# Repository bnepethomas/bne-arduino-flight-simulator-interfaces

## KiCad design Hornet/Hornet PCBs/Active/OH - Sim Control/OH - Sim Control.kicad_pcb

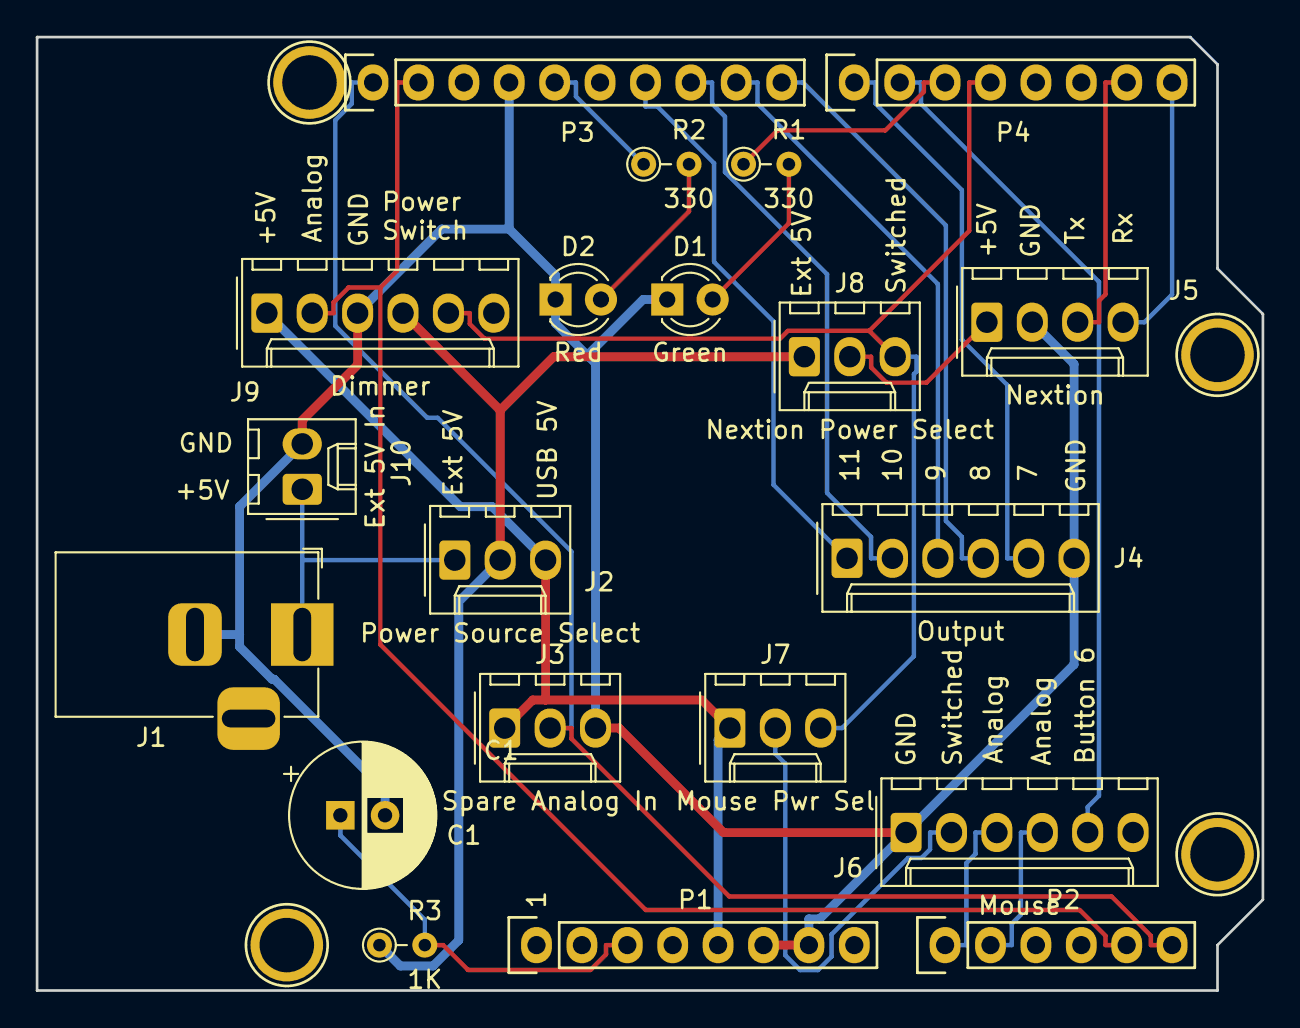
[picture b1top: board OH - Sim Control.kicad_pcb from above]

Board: 2 copper layers, 68.6 x 53.3 mm, 24 parts (0 on the bottom side), 24 nets.

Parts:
C1: CP; PT_CP_Radial_D8.0mm_P2.50mm
D1: Green; LED_D3.0mm
D2: Red; LED_D3.0mm
J1: Ext 5V In; BarrelJack_Horizontal
J2: Power Source Select; Molex_1x03_P2.54mm_Vertical
J3: Spare Analog In; Molex_1x03_P2.54mm_Vertical
J4: Output; Molex_1x06_P2.54mm_Vertical
J5: Nextion; Molex_1x04_P2.54mm_Vertical
J6: Mouse; Molex_1x06_P2.54mm_Vertical
J7: Mouse Pwr Sel; Molex_1x03_P2.54mm_Vertical
J8: Nextion Power Select; Molex_1x03_P2.54mm_Vertical
J9: Dimmer; Molex_1x06_P2.54mm_Vertical
J10: Ext 5V In; Molex_1x02_P2.54mm_Vertical
P1: Power; Socket_Strip_Arduino_1x08
P2: Analog; Socket_Strip_Arduino_1x06
P3: Digital; Socket_Strip_Arduino_1x10
P4: Digital; Socket_Strip_Arduino_1x08
P5, P6, P7, P8: CONN_01X01; Arduino_1pin
R1, R2: 330; PT_R_Axial_DIN0204_L3.6mm_D1.6mm_P2.54mm_Vertical
R3: 1K; PT_R_Axial_DIN0204_L3.6mm_D1.6mm_P2.54mm_Vertical

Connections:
+5V: J2.3, J3.1, J7.1, J9.1, P1.5
+5VD: J2.2, J8.1, J9.4, R3.1
/0(Rx): J5.4, P4.8
/1(Tx): J5.3, P4.7
/5(**): P4.3, R1.1
/6: J6.5, P4.2
/7: J4.5, P4.1
/8: J4.4, P3.10
/9: J4.3, P3.9
/10: J4.2, P3.8
/11: J4.1, P3.7
/13(SCK): P3.5, R2.1
/A0: J6.3, P2.1
/A1: J6.4, P2.2
/A4(SDA): J9.2, P2.5, P3.2
/A5(SCL): J3.2, P2.6, P3.1
/Reset: C1.1, P1.3, R3.2
/Swtiched_5VD: J7.3, J8.3, J9.5, P4.4
GND: C1.2, D1.1, D2.1, J1.2, J3.3, J4.6, J5.2, J6.1, J9.3, J10.2, P1.6, P1.7, P3.4
unnamed: D1.2, R1.2
unnamed: D2.2, R2.2
unnamed: J1.1, J2.1, J10.1
unnamed: J5.1, J8.2
unnamed: J6.2, J7.2

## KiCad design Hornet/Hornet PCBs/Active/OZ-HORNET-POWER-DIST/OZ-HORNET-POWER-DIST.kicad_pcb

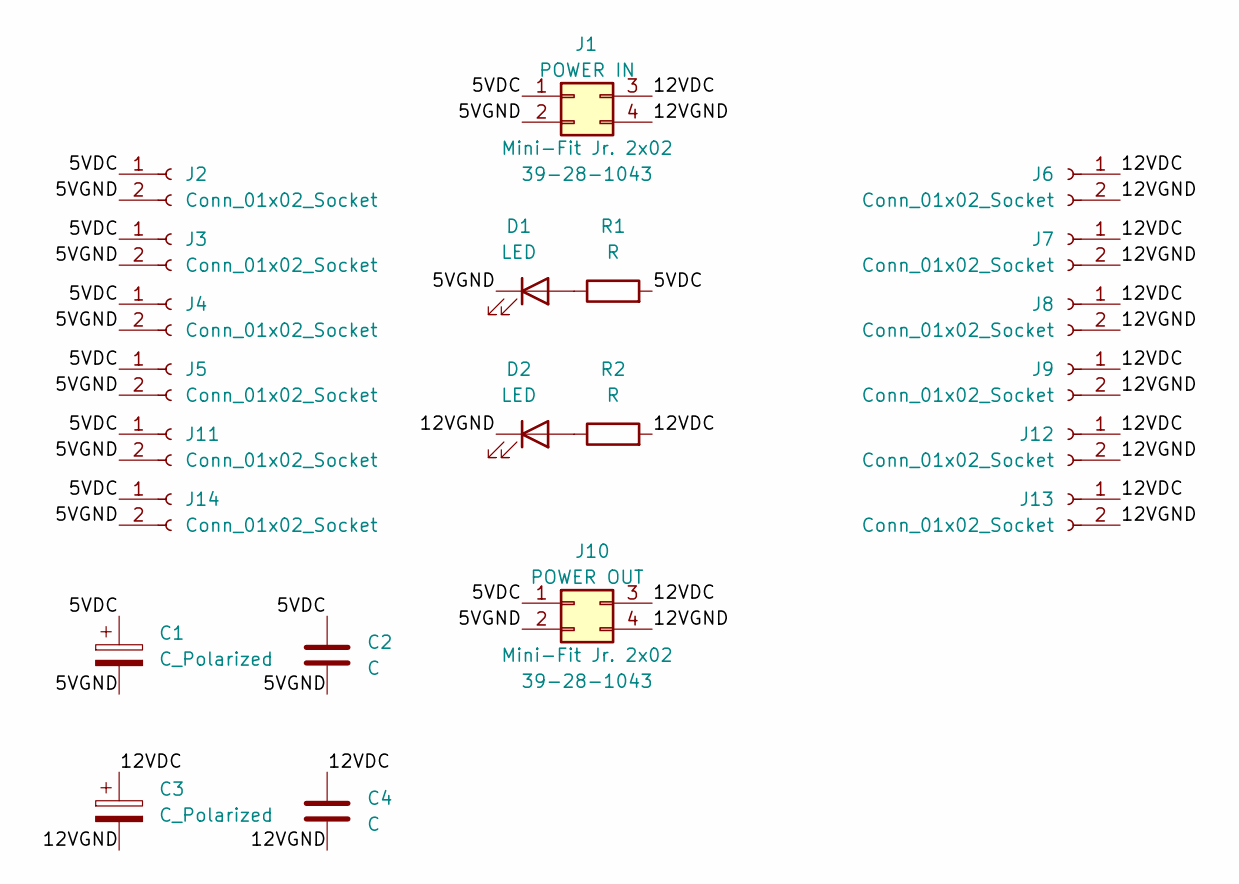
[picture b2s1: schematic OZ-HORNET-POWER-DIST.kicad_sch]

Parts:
C1, C3: C_Polarized; CP_Radial_D6.3mm_P2.50mm
C2, C4: C; C_Disc_D5.0mm_W2.5mm_P2.50mm
D1, D2: LED; LED_D3.0mm
J1, J10: Mini-Fit Jr. 2x02; Aliexpress_Mini-Fit_Jr_5566-04A_2x02_P4.20mm_Vertical; Manufacturer PN 39-28-1043; LCSC C293502
J2, J3, J4, J5, J6, J7, J8, J9, J11, J12, J13, J14: Conn_01x02_Socket; BarrelJack_Horizontal
R1, R2: R; R_Axial_DIN0204_L3.6mm_D1.6mm_P5.08mm_Horizontal

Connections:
/5VDC: C1.1, C2.1, J1.1, J2.1, J3.1, J4.1, J5.1, J10.1, J11.1, J14.1, R1.2
/5VGND: C1.2, C2.2, D1.1 (K), J1.2 (Pin_3), J2.2, J3.2, J4.2, J5.2, J10.2 (Pin_3), J11.2, J14.2
/12VDC: C3.1, C4.1, J1.3 (Pin_2), J6.1, J7.1, J8.1, J9.1, J10.3 (Pin_2), J12.1, J13.1, R2.2
/12VGND: C3.2, C4.2, D2.1 (K), J1.4, J6.2, J7.2, J8.2, J9.2, J10.4, J12.2, J13.2
unnamed: D1.2 (A), R1.1
unnamed: D2.2 (A), R2.1

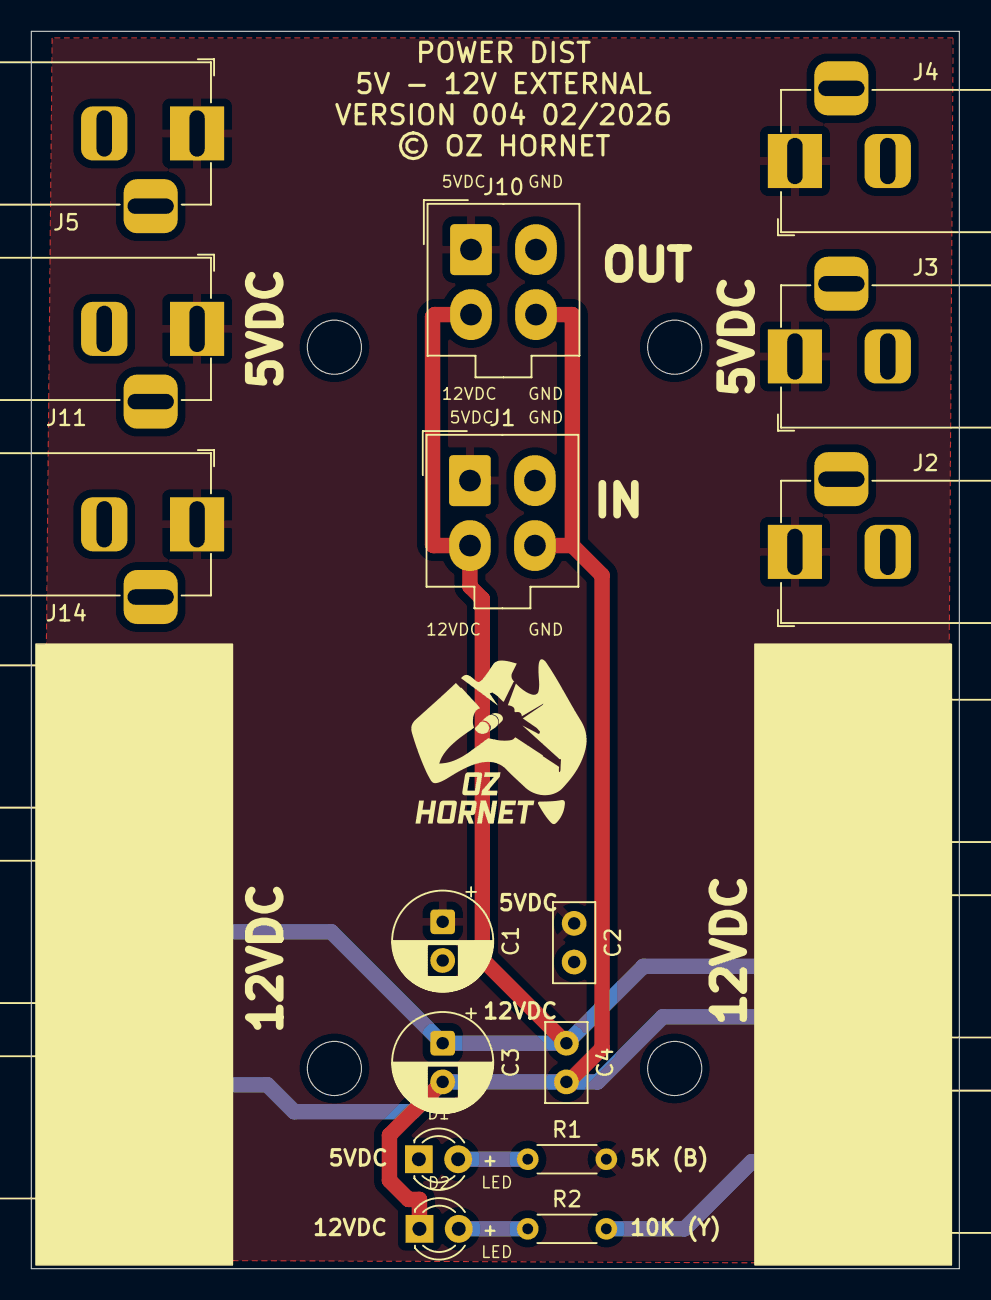
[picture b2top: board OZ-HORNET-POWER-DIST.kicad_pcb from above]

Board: 2 copper layers, 60.0 x 80.0 mm, 22 parts (0 on the bottom side), 6 nets.

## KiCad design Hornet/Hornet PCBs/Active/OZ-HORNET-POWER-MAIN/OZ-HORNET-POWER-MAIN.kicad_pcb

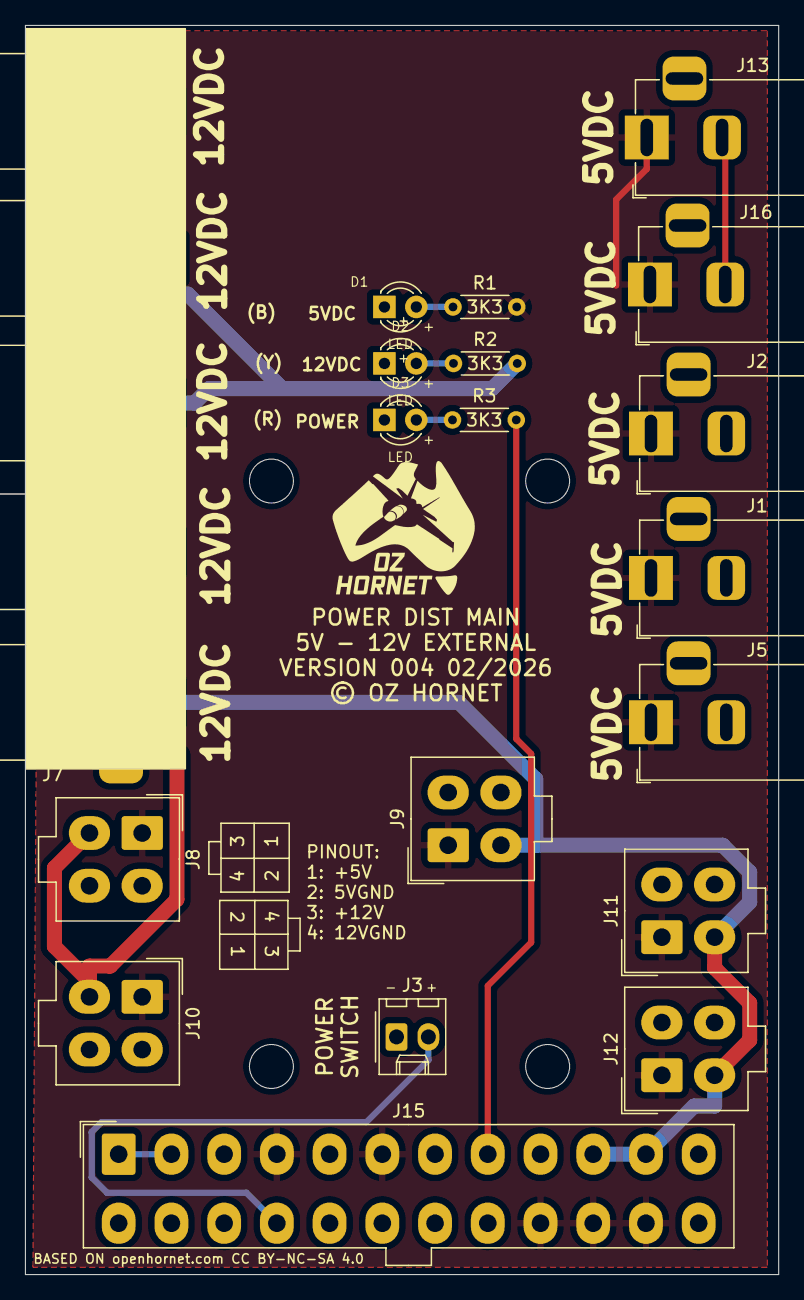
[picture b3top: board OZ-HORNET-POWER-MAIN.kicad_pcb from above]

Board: 2 copper layers, 60.0 x 99.5 mm, 23 parts (0 on the bottom side), 9 nets.

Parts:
D1, D2, D3: LED; LED_D3.0mm
J1, J2, J5, J13, J16: 5V; BarrelJack_Horizontal
J3: Conn_01x02_Female; Molex_KK-254_AE-6410-02A_1x02_P2.54mm_Vertical
J4, J6, J7, J14, J17: 12V; BarrelJack_Horizontal
J8, J9, J10, J11, J12: Mini-Fit Jr. 2x02; Aliexpress_Mini-Fit_Jr_5566-04A_2x02_P4.20mm_Vertical
J15: Conn_01x24_Female; Molex_Mini-Fit_Jr_5566-24A_2x12_P4.20mm_Vertical
R1, R2, R3: 3K3; R_Axial_DIN0204_L3.6mm_D1.6mm_P5.08mm_Horizontal

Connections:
/3.3VDC: J15.1, J15.2
/5VDC: J1.1, J2.1, J5.1, J8.1, J9.1, J10.1, J11.1, J12.1, J13.1, J15.4, J15.6, J15.21, J15.22, J15.23, J16.1, R1.2
/12VDC: J4.1, J6.1, J7.1, J8.3 (Pin_2), J9.3 (Pin_2), J10.3 (Pin_2), J11.3 (Pin_2), J12.3 (Pin_2), J14.1, J15.10, J15.11, J17.1, R2.2
/GND: D1.1 (K), D2.1 (K), D3.1 (K), J1.2, J2.2, J3.1, J4.2, J5.2, J6.2, J7.2, J8.2 (Pin_3), J8.4, J9.2 (Pin_3), J9.4, J10.2 (Pin_3), J10.4, J11.2 (Pin_3), J11.4, J12.2 (Pin_3), J12.4, J13.2, J14.2, J15.3, J15.5, J15.7, J15.15, J15.17, J15.18, J15.19, J15.24, J16.2, J17.2
/POWER: J15.8, R3.2
/PSUSW: J3.2, J15.16
unnamed: D1.2 (A), R1.1
unnamed: D2.2 (A), R2.1
unnamed: D3.2 (A), R3.1

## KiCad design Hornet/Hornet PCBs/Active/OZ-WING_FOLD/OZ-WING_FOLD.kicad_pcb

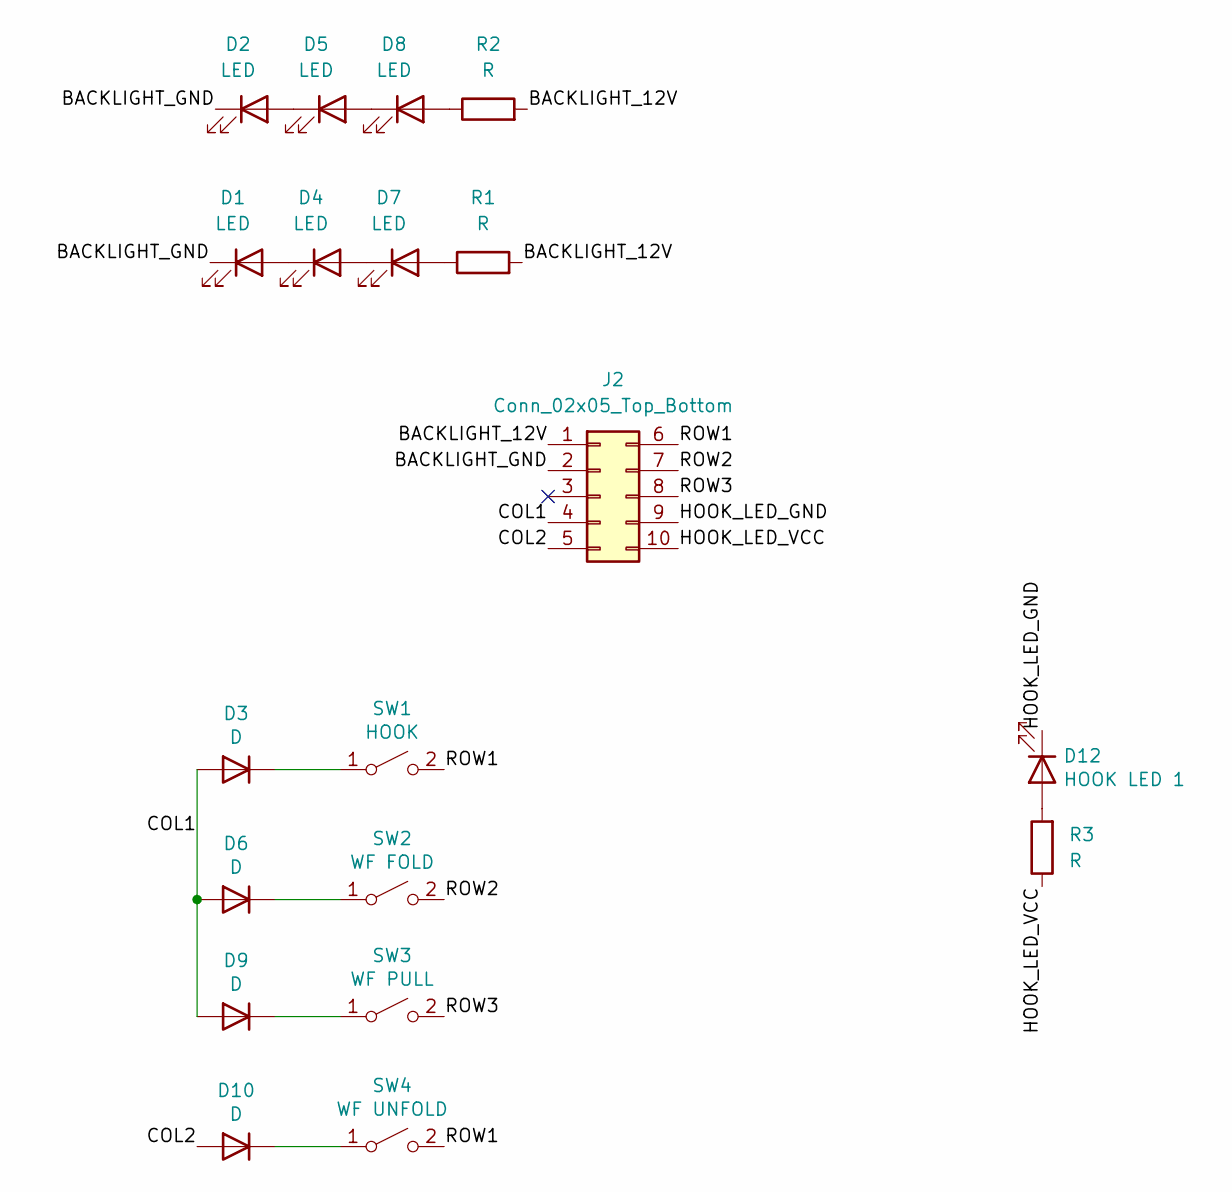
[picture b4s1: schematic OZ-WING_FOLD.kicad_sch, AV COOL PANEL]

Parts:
D1, D2, D4, D5, D7, D8: LED; LED_D3.0mm_FlatTop
D3, D6, D9, D10: D; D_0805_2012Metric
D12: HOOK LED 1; JST_XH_B2B-XH-A_1x02_P2.50mm_Vertical
J2: Conn_02x05_Top_Bottom; IDC-Header_2x05_P2.54mm_Vertical
R1, R2, R3: R; R_0805_2012Metric
SW1: HOOK; JST_XH_B2B-XH-A_1x02_P2.50mm_Vertical
SW2: WF FOLD; JST_XH_B2B-XH-A_1x02_P2.50mm_Vertical
SW3: WF PULL; JST_XH_B2B-XH-A_1x02_P2.50mm_Vertical
SW4: WF UNFOLD; JST_XH_B2B-XH-A_1x02_P2.50mm_Vertical

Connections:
/BACKLIGHT_12V: J2.1, R1.2, R2.2
/BACKLIGHT_GND: D1.1 (K), D2.1 (K), J2.2
/COL1: D3.2 (A), D6.2 (A), D9.2 (A), J2.4
/COL2: D10.2 (A), J2.5
/HOOK_LED_GND: D12.1 (K), J2.9
/HOOK_LED_VCC: J2.10, R3.1
/ROW1: J2.6, SW1.2 (B), SW4.2 (B)
/ROW2: J2.7, SW2.2 (B)
/ROW3: J2.8, SW3.2 (B)
unnamed: D1.2 (A), D4.1 (K)
unnamed: D2.2 (A), D5.1 (K)
unnamed: D3.1 (K), SW1.1 (A)
unnamed: D4.2 (A), D7.1 (K)
unnamed: D5.2 (A), D8.1 (K)
unnamed: D6.1 (K), SW2.1 (A)
unnamed: D7.2 (A), R1.1
unnamed: D8.2 (A), R2.1
unnamed: D9.1 (K), SW3.1 (A)
unnamed: D10.1 (K), SW4.1 (A)
unnamed: D12.2 (A), R3.2

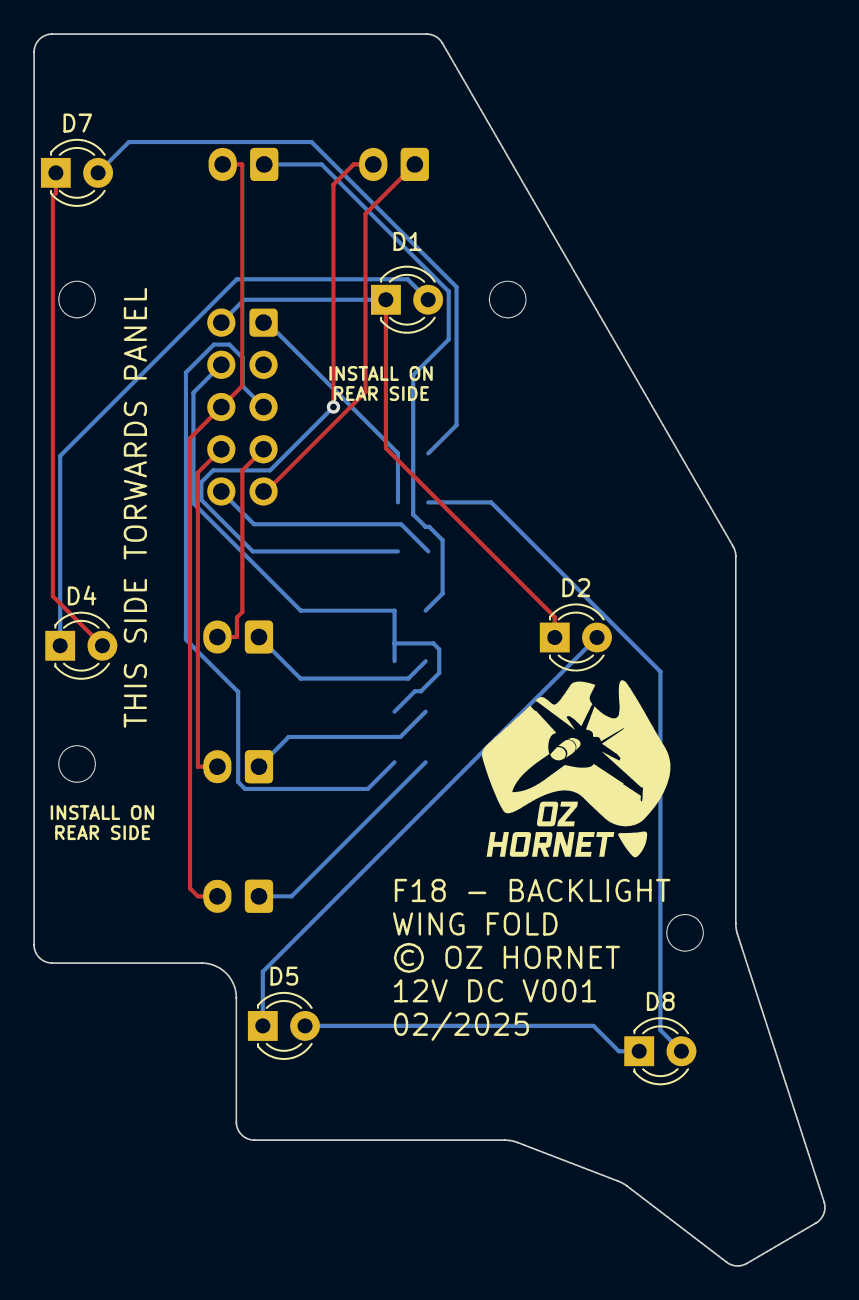
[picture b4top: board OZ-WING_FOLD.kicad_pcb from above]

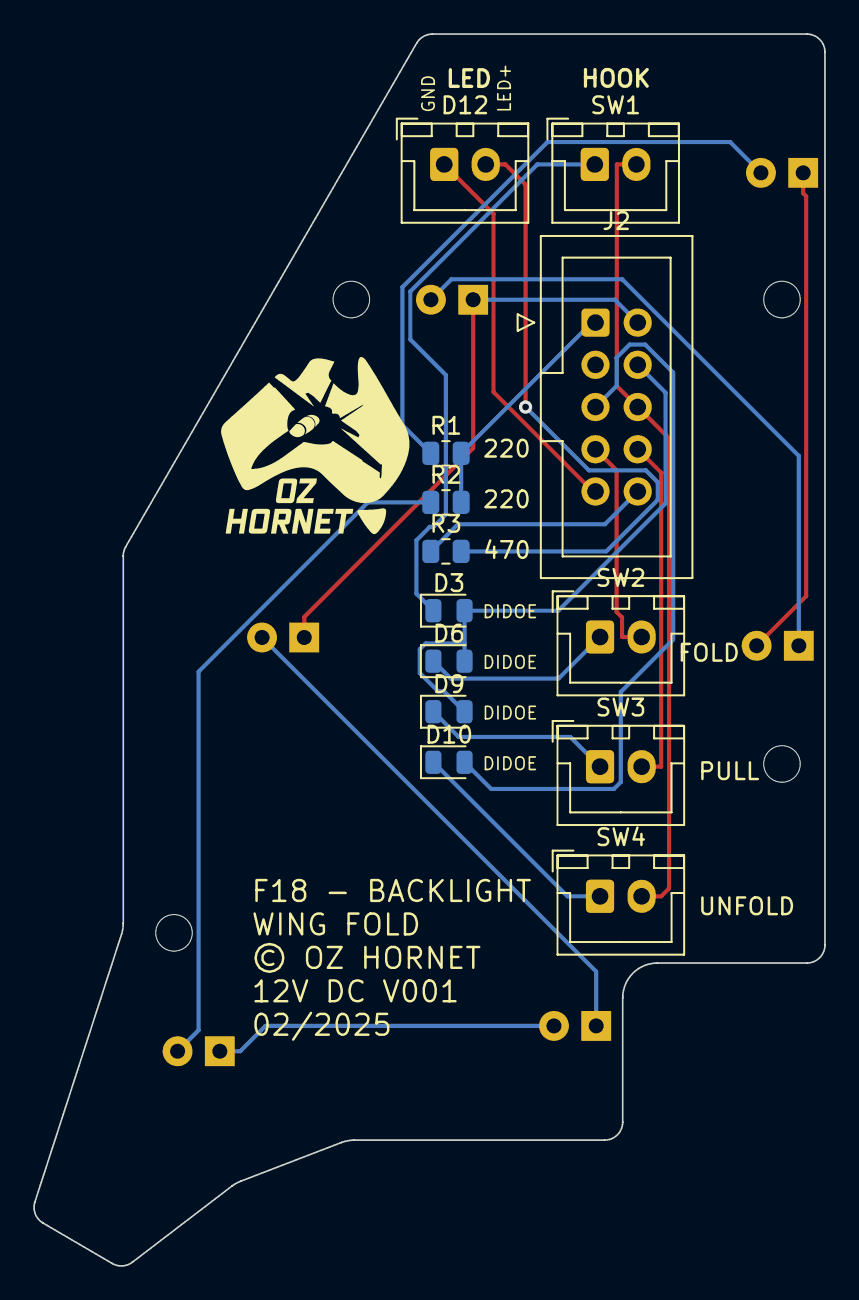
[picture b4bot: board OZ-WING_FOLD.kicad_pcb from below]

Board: 2 copper layers, 47.6 x 74.1 mm, 19 parts (13 on the bottom side), 20 nets.

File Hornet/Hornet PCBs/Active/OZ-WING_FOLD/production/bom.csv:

Designator,Footprint,Quantity,Value,LCSC Part #
"D1, D2, D4, D5, D7, D8",LED_D3.0mm_FlatTop,6,LED,
"D10, D3, D6, D9",0805,4,D,
D12,JST_XH_B2B-XH-A_1x02_P2.50mm_Vertical,1,HOOK LED 1,
J2,IDC-Header_2x05_P2.54mm_Vertical,1,Conn_02x05_Top_Bottom,
"R1, R2, R3",0805,3,R,
SW1,JST_XH_B2B-XH-A_1x02_P2.50mm_Vertical,1,HOOK,
SW2,JST_XH_B2B-XH-A_1x02_P2.50mm_Vertical,1,WF FOLD,
SW3,JST_XH_B2B-XH-A_1x02_P2.50mm_Vertical,1,WF PULL,
SW4,JST_XH_B2B-XH-A_1x02_P2.50mm_Vertical,1,WF UNFOLD,

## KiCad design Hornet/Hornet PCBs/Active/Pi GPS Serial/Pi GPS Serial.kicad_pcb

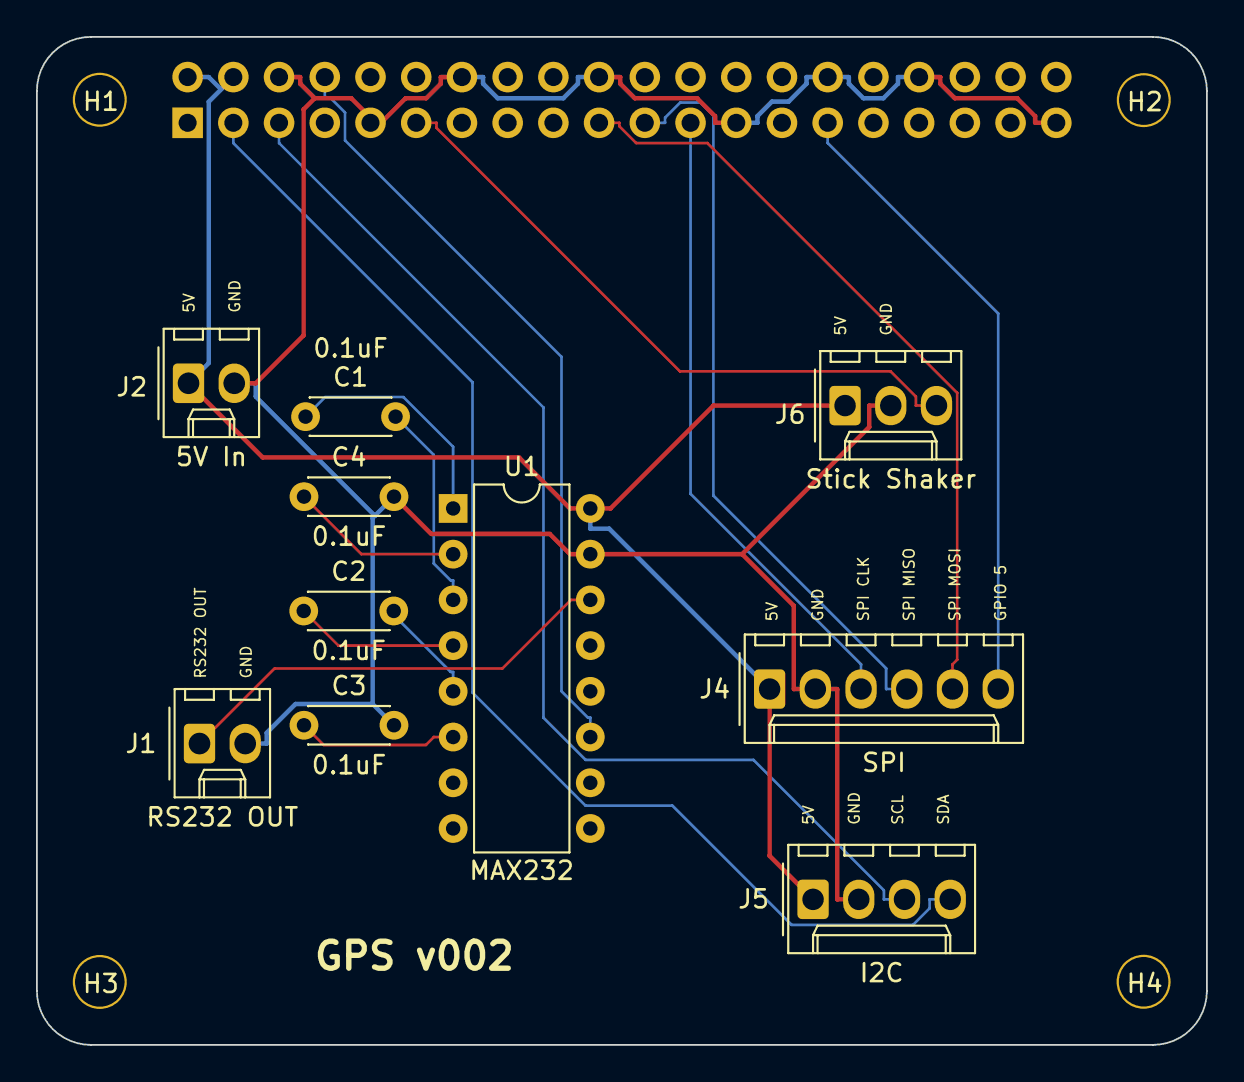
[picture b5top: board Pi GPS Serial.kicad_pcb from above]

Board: 2 copper layers, 65.0 x 56.0 mm, 15 parts (1 on the bottom side), 17 nets.

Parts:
C1, C2, C3, C4: 0.1uF; C_Disc_D4.3mm_W1.9mm_P5.00mm
H1, H2, H3, H4: 3mm_Mounting_Hole; NPTH_3mm_ID
J1: RS232 OUT; Molex_1x02_P2.54mm_Vertical
J2: 5V In; Molex_1x02_P2.54mm_Vertical
J3: 40HAT; PinSocket_2x20_P2.54mm_Vertical
J4: SPI; Molex_KK-254_AE-6410-06A_1x06_P2.54mm_Vertical
J5: I2C; Molex_KK-254_AE-6410-04A_1x04_P2.54mm_Vertical
J6: Stick Shaker; Molex_KK-254_AE-6410-03A_1x03_P2.54mm_Vertical
U1: MAX232; DIP-16_W7.62mm

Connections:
/GPIO5: J3.29 (BCM5), J4.6
/GPIO_GEN0: J3.11 (BCM17), J6.3
/P5V_HAT: J2.1, J3.2 (P5V), J3.4 (P5V), J4.1, J5.1, J6.1, U1.16 (VCC)
/SCL1: J3.5 (BCM3), J5.3
/SDA1: J3.3 (BCM2), J5.4
/SERIAL_TX: J3.8 (BCM14), U1.11 (T1IN)
/SPI_CLK: J3.23 (BCM11), J4.3
/SPI_MISO: J3.21 (BCM9), J4.4
/SPI_MOSI: J3.19 (BCM10), J4.5
GND: C3.2, C4.2, J1.2, J2.2, J3.6 (GND), J3.9 (GND), J3.14 (GND), J3.20 (GND), J3.25 (GND), J3.30 (GND), J3.34 (GND), J3.39 (GND), J4.2, J5.2, J6.2, U1.15 (GND)
unnamed: C1.1, U1.1 (C1+)
unnamed: C1.2, U1.3 (C1-)
unnamed: C2.1, U1.4 (C2+)
unnamed: C2.2, U1.5 (C2-)
unnamed: C3.1, U1.6 (VS-)
unnamed: C4.1, U1.2 (VS+)
unnamed: J1.1, U1.14 (T1OUT)

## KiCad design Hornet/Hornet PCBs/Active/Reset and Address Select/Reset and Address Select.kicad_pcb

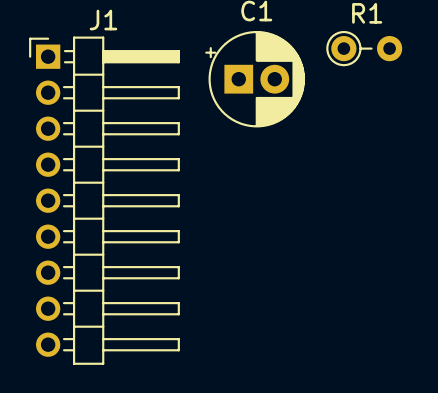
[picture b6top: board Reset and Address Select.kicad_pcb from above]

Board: 2 copper layers, 3 parts (0 on the bottom side), 3 nets, no tracks yet.

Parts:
C1: CP; CP_Radial_D5.0mm_P2.00mm
J1: Conn_01x06_Male; PinHeader_1x09_P2.00mm_Horizontal
R1: R_Small; R_Axial_DIN0204_L3.6mm_D1.6mm_P2.54mm_Vertical

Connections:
unnamed: C1.1, R1.2
unnamed: C1.2, J1.4
unnamed: J1.1, R1.1

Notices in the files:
Hornet/Hornet PCBs/Active/OZ-HORNET-POWER-DIST/OZ-HORNET-POWER-DIST.kicad_pcb:
© OZ HORNET
Hornet/Hornet PCBs/Active/OZ-HORNET-POWER-MAIN/OZ-HORNET-POWER-MAIN.kicad_pcb:
BASED ON openhornet.com CC BY-NC-SA 4.0
Hornet/Hornet PCBs/Active/OZ-WING_FOLD/OZ-WING_FOLD.kicad_pcb:
License:  CC BY-NC-SA
